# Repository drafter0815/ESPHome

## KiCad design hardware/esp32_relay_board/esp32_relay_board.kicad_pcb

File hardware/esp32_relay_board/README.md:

# ESP32 Touch Relay Controller – KiCad Startprojekt

Dieses Verzeichnis enthaelt ein hierarchisches KiCad-6/7-Projekt als Ausgangspunkt fuer die weitere Entwicklung einer Platine mit ESP32, 3" Touchdisplay, 16 Relais und 4 Servokanälen.

## Dateien

- `esp32_relay_board.kicad_pro` – Projektdatei zum Oeffnen in KiCad.
- `esp32_relay_board.kicad_sch` – Haupthierarchie mit Unterblaettern.
- `esp32_relay_board.kicad_pcb` – Geroutetes Referenz-Layout mit 3 Stiftsockelleisten (Steuerung, Treiber, Last) und exemplarischen Busführungen.
- `esp32_relay_board_detail.txt` – Reines Text-Blueprint in ASCII, erzeugt durch `scripts/generate_ascii.py`, funktioniert auch, wenn keinerlei Binärdateien übertragen werden dürfen.
- `sym-lib-table` – Lokale Symboltabelle, die alle verwendeten KiCad-Standardbibliotheken bindet.
- `power.kicad_sch` – Platzhalter fuer Netzteil- und Schutzbeschaltung.
- `mcu_display.kicad_sch` – Platzhalter fuer ESP32, Display und Touch.
- `relays.kicad_sch` – Platzhalter fuer Optokoppler- und Relaisstufe.
- `servo_i2c.kicad_sch` – Platzhalter fuer PCA9685 und Servoanschluesse.
- `scripts/generate_board.py` – Reines Python-Skript (ohne KiCad-Abhängigkeiten), das die KiCad-PCB-Datei inklusive Steckverbindern und Leiterbahnen neu generiert.

## Kompatibilitaet

Die Schaltpläne liegen jetzt bereits im modernen **S-Expression-Format** (KiCad 7+) vor und lassen sich direkt ohne Fehlermeldung mit `kicad-cli` oder in der KiCad-GUI öffnen. Ein begleitendes Skript (`scripts/convert_legacy_sch.py`) dokumentiert den Migrationsweg aus den ursprünglichen V4-Dateien und erlaubt bei Bedarf die erneute Konvertierung.

## Weiteres Vorgehen

1. Falls du das Referenzlayout frisch erzeugen moechtest, fuehre in diesem Ordner `python3 scripts/generate_board.py` aus. Das Skript schreibt die komplette `.kicad_pcb`-Datei neu und benoetigt keine KiCad-Installation.
2. Fuer eine schnelle textuelle Vorschau kannst du optional `python3 scripts/generate_ascii.py` ausführen; dabei entsteht bzw. aktualisiert sich `esp32_relay_board_detail.txt`.
3. Oeffne danach `esp32_relay_board.kicad_pro` in KiCad 6 oder neuer.
4. Folge den Hinweisen in `NOTES.md`, um Bauteile, Netznamen und Schutzbeschaltungen gezielt zu platzieren.
5. Definiere die genauen Netzbezeichnungen und Steckverbinder entsprechend deiner Mechanik.
6. Erstelle anschliessend ein neues PCB und synchronisiere das Netz aus dem Schaltplan.

> Hinweis: In dieser Umgebung laesst sich KiCad selbst nicht ausfuehren. Das bereitgestellte Projekt dient daher als sauber strukturierter Startpunkt, den du lokal in KiCad oder Altium weiterverarbeiten kannst.

## KiCad-Bibliotheken beziehen

Falls dir lokal die offiziellen KiCad-Bibliotheken fehlen, findest du im Unterordner `scripts/` das Skript `clone_kicad_libs.sh`. Fuehre es in einem leeren Verzeichnis mit Internetzugang aus, um alle offiziellen Symbol- und Footprint-Repositorys von GitHub zu klonen und auf den neuesten Stand zu bringen.

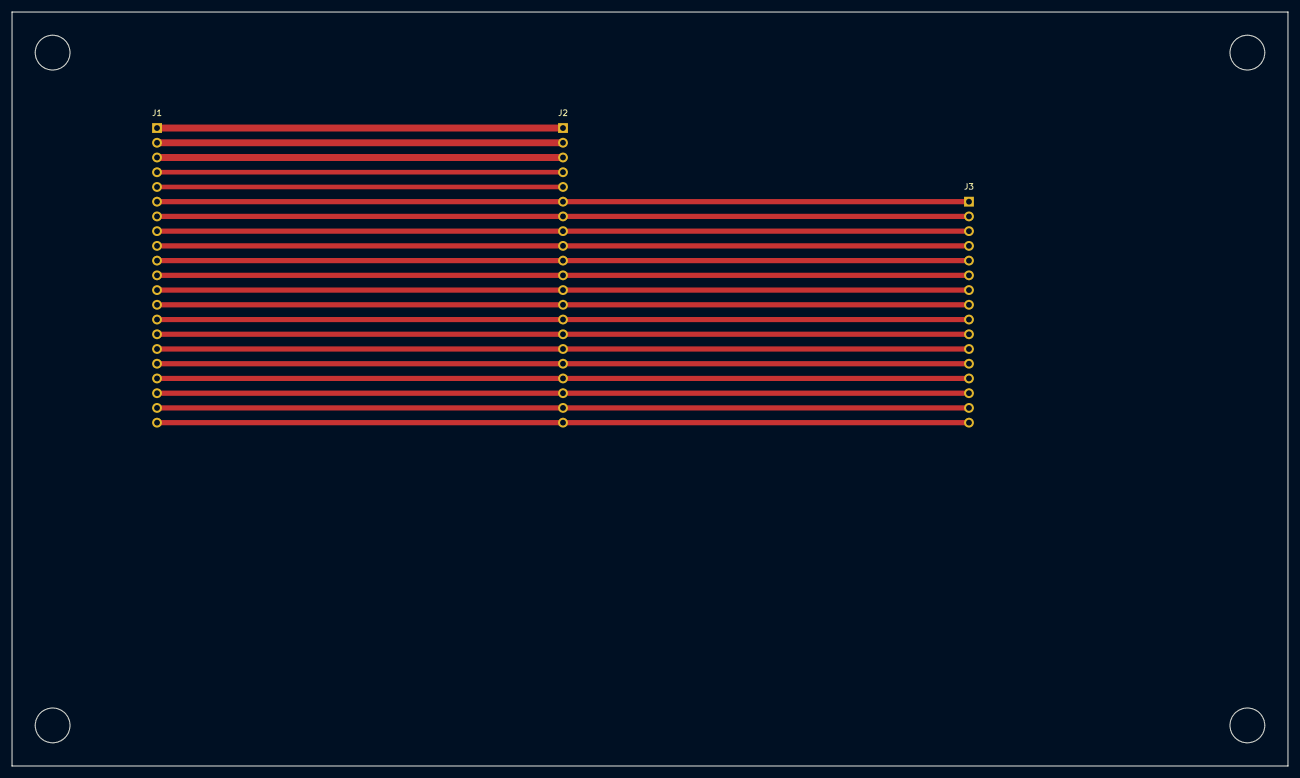
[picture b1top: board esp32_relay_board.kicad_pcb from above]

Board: 2 copper layers, 220.0 x 130.0 mm, 3 parts (0 on the bottom side), 21 nets.

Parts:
J1: ESP32_CTRL; PinHeader_1x21_P2.54mm
J2: RELAY_DRIVER; PinHeader_1x21_P2.54mm
J3: LOAD_HEADER; PinHeader_1x16_P2.54mm

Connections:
GND: J1.1, J2.1
RELAY01: J1.6, J2.6, J3.1
RELAY02: J1.7, J2.7, J3.2
RELAY03: J1.8, J2.8, J3.3
RELAY04: J1.9, J2.9, J3.4
RELAY05: J1.10, J2.10, J3.5
RELAY06: J1.11, J2.11, J3.6
RELAY07: J1.12, J2.12, J3.7
RELAY08: J1.13, J2.13, J3.8
RELAY09: J1.14, J2.14, J3.9
RELAY10: J1.15, J2.15, J3.10
RELAY11: J1.16, J2.16, J3.11
RELAY12: J1.17, J2.17, J3.12
RELAY13: J1.18, J2.18, J3.13
RELAY14: J1.19, J2.19, J3.14
RELAY15: J1.20, J2.20, J3.15
RELAY16: J1.21, J2.21, J3.16
SCL: J1.4, J2.4
SDA: J1.5, J2.5
V5: J1.2, J2.2
V12: J1.3, J2.3

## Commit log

2025-10-20 Create test
2025-10-20 Add KiCad project skeleton for ESP32 relay controller
2025-10-20 Document KiCad follow-up steps
2025-10-20 Add KiCad library clone helper script
2025-10-20 Add illustrative PCB layout guide
2025-10-20 Generate ESP32 relay board via KiCad CLI script
2025-10-20 Add CLI-friendly SVG export for ESP32 board
2025-10-22 Add routed header concept and drop binary exports
2025-10-22 Rewrite KiCad schematics in legacy format
2025-10-22 Add library declarations to KiCad schematics
2025-10-23 Migrate schematics to KiCad 7 format
